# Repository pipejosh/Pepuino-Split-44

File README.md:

### Pepuino Split 44

This is a custom wireless keyboard inpired in the corne and sofle layout so my wrists arent crippled anymore!
A 44 keys keybaord wireless powered by a super mini (the cheapest BT microcontroller I could find) its wirelessssssss btw!
Featuring really cool art and bluetooth connectivity!

### Images

## IRL BUILD!

## Render

## Case

## PCB

## Schematic

## BOM

### Components List

| Name | Purpose | Quantity | Total Cost (USD) | Distributor | Link |
| :--- | :--- | :---: | :---: | :--- | :--- |
| **m2 5mm standoff** | Assembly | 50 | $2.21 | AliExpress | [Link](https://www.aliexpress.com/item/32975966103.html) |
| **m2 2mm screw** | Assembly | 50 | $1.79 | AliExpress | [Link](https://www.aliexpress.com/item/1005005070119421.html) |
| **THT 4.7K resistor** | Pull-up resistor | 20 | $1.77 | AliExpress | [Link](https://www.aliexpress.com/item/1005006704431738.html) |
| **0805 2M Resistor** | Voltage divider | 100 | $1.55 | AliExpress | [Link](https://www.aliexpress.com/item/1005004145810949.html) |
| **0805 820K Resistor** | Voltage divider | 100 | $1.79 | AliExpress | [Link](https://www.aliexpress.com/item/1005004145810949.html) |
| **Battery 3.7V 110mAh** | Keyboard power | 2 | $8.87 | AliExpress | [Link](https://www.google.com/search?q=https://www.aliexpress.com/item/1005011794722407.html) |
| **MSK-12D19** | Slide switch | 20 | $2.05 | AliExpress | [Link](https://www.aliexpress.com/item/1005009651088272.html) |
| **Switches** | Bao Bao Dragon | 45 | $10.95 | AliExpress | [Link](https://www.aliexpress.com/item/1005012005250603.html) |
| **Reset Button** | Reset button | 10 | $2.70 | AliExpress | [Link](https://www.aliexpress.com/item/1005009739698023.html) |
| **SK6812 MINI-E RGB** | RGB Lighting | 50 | $3.86 | AliExpress | [Link](https://www.google.com/search?q=https://www.aliexpress.com/item/1005005193716172.html) |
| **1N4148W T4 SOD-123** | Diodes | 100 | $3.18 | AliExpress | [Link](https://www.aliexpress.com/item/1005007160563285.html) |
| **Hotswap sockets** | Easy replace switches | 50 | $10.13 | AliExpress | [Link](https://www.google.com/search?q=https://www.aliexpress.com/item/1005009254258549.html) |
| **OLED 0.91"** | Display | 2 | $5.52 | AliExpress | [Link](https://www.google.com/search?q=https://www.aliexpress.com/item/1005011783382489.html) |
| **Super mini NRF52840** | Microcontroller | 2 | $5.30 | AliExpress | [Link](https://www.aliexpress.com/item/1005007078900079.html) |
| **Components Subtotal** | | | $61.67 | | |

-----

### PCB Manufacturing

| Name | Purpose | Quantity | Manufacturing | Shipping | Total Cost (USD) | Distributor |
| :--- | :--- | :---: | :---: | :---: | :---: | :--- |
| **PCB** | The main circuit board | 5 | $20.00 | $13.26 | $33.26 | JLCPCB |

-----

**Grand Total Project Estimate Cost: $94.93**

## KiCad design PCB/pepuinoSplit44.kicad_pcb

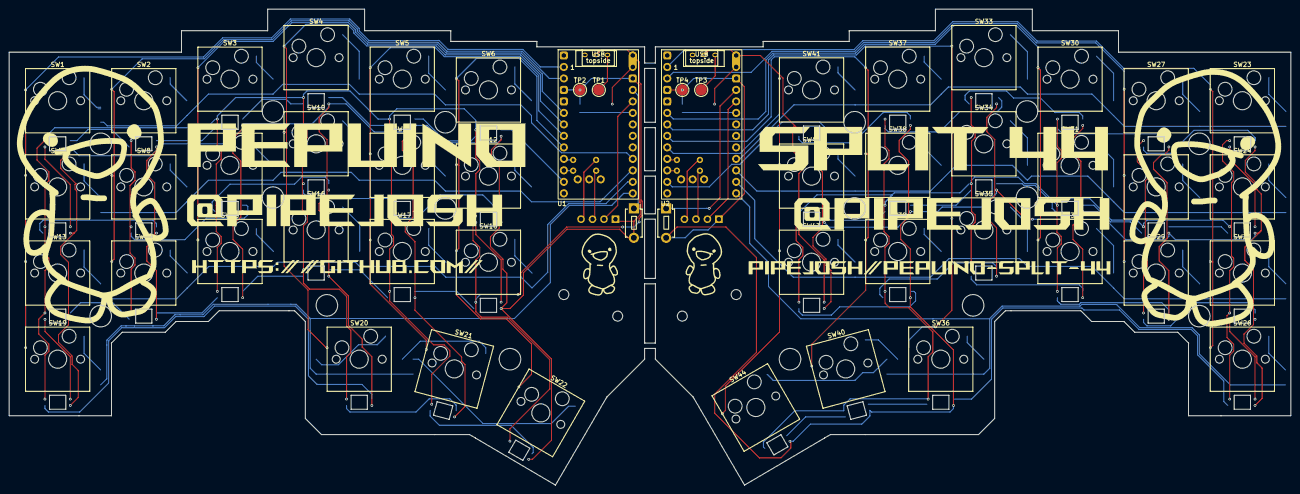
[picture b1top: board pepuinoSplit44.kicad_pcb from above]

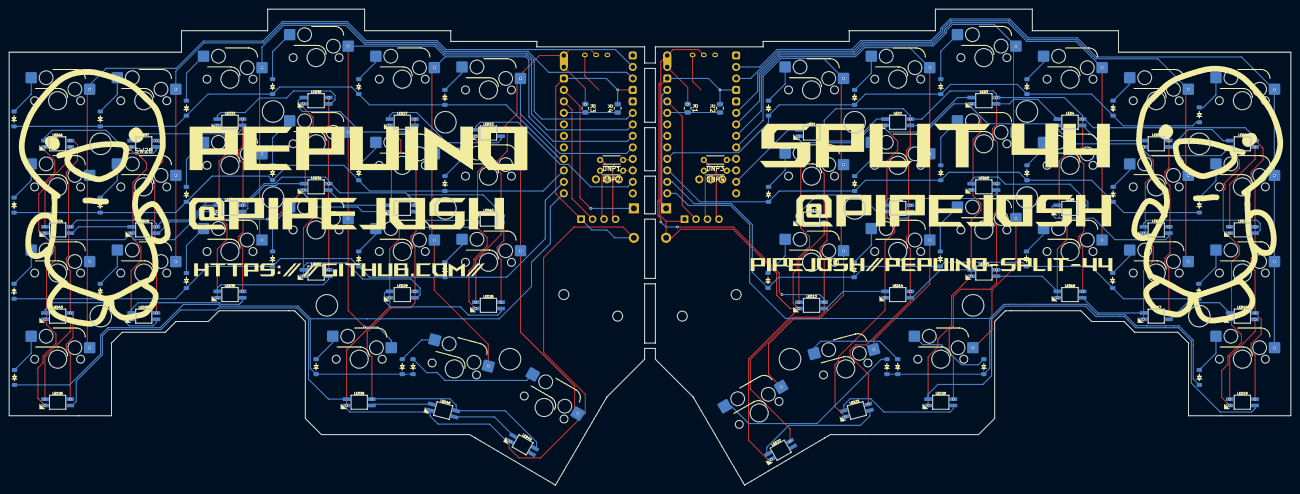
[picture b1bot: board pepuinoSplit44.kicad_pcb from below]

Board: 2 copper layers, 283.3 x 105.2 mm, 156 parts (96 on the bottom side), 128 nets.

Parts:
D1, D2, D3, D4, D5, D6, D7, D8, D9, D10, D11, D12, D13, D14, D15, D16, D17, D18, D19, D20, D21, D22, D23, D24, D25, D26, D27, D28, D29, D30, D31, D32, D33, D34, D35, D36, D37, D38, D39, D40, D41, D42, D43, D44: Diode_SOD-123
DNP1, DNP2, DNP3, DNP4: DNP; R_Axial_DIN0204_L3.6mm_D1.6mm_P5.08mm_Horizontal
H1, H2, H3, H4: MountingHole; MountingHole_2.2mm_M2
J1, J2: OLED_128x32
LED1, LED2, LED3, LED4, LED5, LED6, LED7, LED8, LED9, LED10, LED11, LED12, LED13, LED14, LED15, LED16, LED17, LED18, LED19, LED20, LED21, LED22, LED23, LED24, LED25, LED26, LED27, LED28, LED29, LED30, LED31, LED32, LED33, LED34, LED35, LED36, LED37, LED38, LED39, LED40, LED41, LED42, LED43, LED44: YS-SK6812MINI-E
R1, R3: 806K; R_0805_2012Metric
R2, R4: 2M; R_0805_2012Metric
S1, S2: EG1218; TGSW_MSK-12D19
SW1, SW2, SW3, SW4, SW5, SW6, SW7, SW8, SW9, SW10, SW11, SW12, SW13, SW14, SW15, SW16, SW17, SW18, SW19, SW20, SW21, SW22, SW23, SW24, SW25, SW26, SW27, SW28, SW29, SW30, SW31, SW32, SW33, SW34, SW35, SW36, SW37, SW38, SW39, SW40, SW41, SW42, SW43, SW44: Switch; Hotswap_MX_1.00u
SW45, SW46: Switch; Button_MJTP1243
TP1, TP2, TP3, TP4: TestPoint; TestPoint_Pad_D2.5mm
U1, U2: SuperMini nRF52840; SuperMini_nRF52840_AH_USBup

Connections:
unnamed: D1.2 (A), SW1.2
unnamed: D2.2 (A), SW2.2
unnamed: D3.2 (A), SW3.2
unnamed: D4.2 (A), SW4.2
unnamed: D5.2 (A), SW5.2
unnamed: D6.2 (A), SW6.2
unnamed: D7.2 (A), SW12.2
unnamed: D8.2 (A), SW11.2
unnamed: D9.2 (A), SW10.2
unnamed: D10.2 (A), SW9.2
unnamed: D11.2 (A), SW8.2
unnamed: D12.2 (A), SW7.2
unnamed: D13.2 (A), SW13.2
unnamed: D14.2 (A), SW14.2
unnamed: D15.2 (A), SW15.2
unnamed: D16.2 (A), SW16.2
unnamed: D17.2 (A), SW17.2
unnamed: D18.2 (A), SW18.2
unnamed: D19.2 (A), SW22.2
unnamed: D20.2 (A), SW21.2
unnamed: D21.2 (A), SW20.2
unnamed: D22.2 (A), SW19.2
unnamed: D23.2 (A), SW23.2
unnamed: D24.2 (A), SW24.2
unnamed: D25.2 (A), SW25.2
unnamed: D26.2 (A), SW26.2
unnamed: D27.2 (A), SW27.2
unnamed: D28.2 (A), SW28.2
unnamed: D29.2 (A), SW29.2
unnamed: D30.2 (A), SW30.2
unnamed: D31.2 (A), SW31.2
unnamed: D32.2 (A), SW32.2
unnamed: D33.2 (A), SW33.2
unnamed: D34.2 (A), SW34.2
unnamed: D35.2 (A), SW35.2
unnamed: D36.2 (A), SW36.2
unnamed: D37.2 (A), SW37.2
unnamed: D38.2 (A), SW38.2
unnamed: D39.2 (A), SW39.2
unnamed: D40.2 (A), SW40.2
unnamed: D41.2 (A), SW41.2
unnamed: D42.2 (A), SW42.2
unnamed: D43.2 (A), SW43.2
unnamed: D44.2 (A), SW44.2
unnamed: DNP4.2, J1.3 (SCL)
unnamed: DNP3.2, J1.4 (SDA)
unnamed: DNP2.2, J2.3 (SCL)
unnamed: DNP1.2, J2.4 (SDA)
unnamed: LED1.2 (DOUT), LED2.4 (DIN)
unnamed: LED2.2 (DOUT), LED3.4 (DIN)
unnamed: LED3.2 (DOUT), LED4.4 (DIN)
unnamed: LED4.2 (DOUT), LED5.4 (DIN)
unnamed: LED5.2 (DOUT), LED6.4 (DIN)
unnamed: LED6.2 (DOUT), LED7.4 (DIN)
unnamed: LED7.2 (DOUT), LED8.4 (DIN)
unnamed: LED8.2 (DOUT), LED9.4 (DIN)
unnamed: LED9.2 (DOUT), LED10.4 (DIN)
unnamed: LED10.2 (DOUT), LED11.4 (DIN)
unnamed: LED11.2 (DOUT), LED12.4 (DIN)
unnamed: LED12.2 (DOUT), LED13.4 (DIN)
unnamed: LED13.2 (DOUT), LED14.4 (DIN)
unnamed: LED14.2 (DOUT), LED15.4 (DIN)
unnamed: LED15.2 (DOUT), LED16.4 (DIN)
unnamed: LED16.2 (DOUT), LED17.4 (DIN)
unnamed: LED17.2 (DOUT), LED18.4 (DIN)
unnamed: LED18.2 (DOUT), LED19.4 (DIN)
unnamed: LED19.2 (DOUT), LED20.4 (DIN)
unnamed: LED20.2 (DOUT), LED21.4 (DIN)
unnamed: LED21.2 (DOUT), LED22.4 (DIN)
unnamed: LED23.2 (DOUT), LED27.4 (DIN)
unnamed: LED24.4 (DIN), LED41.2 (DOUT)
unnamed: LED24.2 (DOUT), LED28.4 (DIN)
unnamed: LED25.4 (DIN), LED42.2 (DOUT)
unnamed: LED25.2 (DOUT), LED29.4 (DIN)
unnamed: LED26.4 (DIN), LED43.2 (DOUT)
unnamed: LED26.2 (DOUT), LED36.4 (DIN)
unnamed: LED27.2 (DOUT), LED30.4 (DIN)
unnamed: LED28.2 (DOUT), LED31.4 (DIN)
unnamed: LED29.2 (DOUT), LED32.4 (DIN)
unnamed: LED30.2 (DOUT), LED33.4 (DIN)
unnamed: LED31.2 (DOUT), LED34.4 (DIN)
unnamed: LED32.2 (DOUT), LED35.4 (DIN)
unnamed: LED33.2 (DOUT), LED37.4 (DIN)
unnamed: LED34.2 (DOUT), LED38.4 (DIN)
unnamed: LED35.2 (DOUT), LED39.4 (DIN)
unnamed: LED36.2 (DOUT), LED40.4 (DIN)
unnamed: LED37.2 (DOUT), LED41.4 (DIN)
unnamed: LED38.2 (DOUT), LED42.4 (DIN)
unnamed: LED39.2 (DOUT), LED43.4 (DIN)
unnamed: LED40.2 (DOUT), LED44.4 (DIN)
unnamed: S1.1, TP1.1 (1_1)
unnamed: S2.1, TP3.1 (1_1)
l_3.3V: J1.2 (VCC), U1.16 (3V3)
l_COL0: SW1.1, SW7.1, SW13.1, SW19.1, U1.1 (P0.06)
l_COL1: SW2.1, SW8.1, SW14.1, U1.2 (P0.08)
l_COL2: SW3.1, SW9.1, SW15.1, U1.5 (P0.17)
l_COL3: SW4.1, SW10.1, SW16.1, SW20.1, U1.6 (P0.20)
l_COL4: SW5.1, SW11.1, SW17.1, SW21.1, U1.7 (P0.22)
l_COL5: SW6.1, SW12.1, SW18.1, SW22.1, U1.8 (P0.24)
l_GND: J1.1 (GND), LED1.3 (VSS), LED2.3 (VSS), LED3.3 (VSS), LED4.3 (VSS), LED5.3 (VSS), LED6.3 (VSS), LED7.3 (VSS), LED8.3 (VSS), LED9.3 (VSS), LED10.3 (VSS), LED11.3 (VSS), LED12.3 (VSS), LED13.3 (VSS), LED14.3 (VSS), LED15.3 (VSS), LED16.3 (VSS), LED17.3 (VSS), LED18.3 (VSS), LED19.3 (VSS), LED20.3 (VSS), LED21.3 (VSS), LED22.3 (VSS), R2.2, SW46.2, TP2.1 (1_1), U1.3 (GND), U1.14 (GND)
l_LED: LED1.4 (DIN), U1.11 (P1.04-LF)
l_ROW0: D1.1 (K), D2.1 (K), D3.1 (K), D4.1 (K), D5.1 (K), D6.1 (K), U1.21 (P1.13-LF)
l_ROW1: D7.1 (K), D8.1 (K), D9.1 (K), D10.1 (K), D11.1 (K), D12.1 (K), U1.22 (P1.11-LF)
l_ROW2: D13.1 (K), D14.1 (K), D15.1 (K), D16.1 (K), D17.1 (K), D18.1 (K), U1.23 (P0.10-LF)
l_ROW3: D19.1 (K), D20.1 (K), D21.1 (K), D22.1 (K), U1.24 (P0.09-LF)
l_RST: SW46.1, U1.15 (RST)
l_SCL: DNP4.1, U1.10 (P0.11)
l_SDA: DNP3.1, U1.9 (P1.00)
l_SENSE: R1.2, R2.1, U1.17 (P0.31-LF)
l_VBAT: LED1.1 (VDD), LED2.1 (VDD), LED3.1 (VDD), LED4.1 (VDD), LED5.1 (VDD), LED6.1 (VDD), LED7.1 (VDD), LED8.1 (VDD), LED9.1 (VDD), LED10.1 (VDD), LED11.1 (VDD), LED12.1 (VDD), LED13.1 (VDD), LED14.1 (VDD), LED15.1 (VDD), LED16.1 (VDD), LED17.1 (VDD), LED18.1 (VDD), LED19.1 (VDD), LED20.1 (VDD), LED21.1 (VDD), LED22.1 (VDD), R1.1, S1.2, U1.13 (BAT+), U1.29 (BAT+)
r_3.3V: J2.2 (VCC), U2.16 (3V3)
r_COL0: SW23.1, SW24.1, SW25.1, SW26.1, U2.1 (P0.06)
r_COL1: SW27.1, SW28.1, SW29.1, U2.2 (P0.08)
r_COL2: SW30.1, SW31.1, SW32.1, U2.5 (P0.17)
r_COL3: SW33.1, SW34.1, SW35.1, SW36.1, U2.6 (P0.20)
r_COL4: SW37.1, SW38.1, SW39.1, SW40.1, U2.7 (P0.22)
r_COL5: SW41.1, SW42.1, SW43.1, SW44.1, U2.8 (P0.24)
r_GND: J2.1 (GND), LED23.3 (VSS), LED24.3 (VSS), LED25.3 (VSS), LED26.3 (VSS), LED27.3 (VSS), LED28.3 (VSS), LED29.3 (VSS), LED30.3 (VSS), LED31.3 (VSS), LED32.3 (VSS), LED33.3 (VSS), LED34.3 (VSS), LED35.3 (VSS), LED36.3 (VSS), LED37.3 (VSS), LED38.3 (VSS), LED39.3 (VSS), LED40.3 (VSS), LED41.3 (VSS), LED42.3 (VSS), LED43.3 (VSS), LED44.3 (VSS), R4.2, SW45.2, TP4.1 (1_1), U2.3 (GND), U2.14 (GND)
r_LED: LED23.4 (DIN), U2.11 (P1.04-LF)
r_ROW0: D23.1 (K), D27.1 (K), D30.1 (K), D33.1 (K), D37.1 (K), D41.1 (K), U2.21 (P1.13-LF)
r_ROW1: D24.1 (K), D28.1 (K), D31.1 (K), D34.1 (K), D38.1 (K), D42.1 (K), U2.22 (P1.11-LF)
r_ROW2: D25.1 (K), D29.1 (K), D32.1 (K), D35.1 (K), D39.1 (K), D43.1 (K), U2.23 (P0.10-LF)
r_ROW3: D26.1 (K), D36.1 (K), D40.1 (K), D44.1 (K), U2.24 (P0.09-LF)
r_RST: SW45.1, U2.15 (RST)
r_SCL: DNP2.1, U2.10 (P0.11)
r_SDA: DNP1.1, U2.9 (P1.00)
r_SENSE: R3.2, R4.1, U2.17 (P0.31-LF)
r_VBAT: LED23.1 (VDD), LED24.1 (VDD), LED25.1 (VDD), LED26.1 (VDD), LED27.1 (VDD), LED28.1 (VDD), LED29.1 (VDD), LED30.1 (VDD), LED31.1 (VDD), LED32.1 (VDD), LED33.1 (VDD), LED34.1 (VDD), LED35.1 (VDD), LED36.1 (VDD), LED37.1 (VDD), LED38.1 (VDD), LED39.1 (VDD), LED40.1 (VDD), LED41.1 (VDD), LED42.1 (VDD), LED43.1 (VDD), LED44.1 (VDD), R3.1, S2.2, U2.13 (BAT+), U2.29 (BAT+)

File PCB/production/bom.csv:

Designator,Footprint,Quantity,Value,LCSC Part #
"D1, D10, D11, D12, D13, D14, D15, D16, D17, D18, D19, D2, D20, D21, D22, D23, D24, D25, D26, D27, D28, D29, D3, D30, D31, D32, D33, D34, D35, D36, D37, D38, D39, D4, D40, D41, D42, D43, D44, D5, D6, D7, D8, D9",Diode_SOD-123,44,~,
"J1, J2",OLED_128x32,2,OLED_128x32,
"LED1, LED10, LED11, LED12, LED13, LED14, LED15, LED16, LED17, LED18, LED19, LED2, LED20, LED21, LED22, LED23, LED24, LED25, LED26, LED27, LED28, LED29, LED3, LED30, LED31, LED32, LED33, LED34, LED35, LED36, LED37, LED38, LED39, LED4, LED40, LED41, LED42, LED43, LED44, LED5, LED6, LED7, LED8, LED9",YS-SK6812MINI-E,44,YS-SK6812MINI-E,
"R1, R3",0805,2,806K,
"R2, R4",0805,2,2M,
"S1, S2",TGSW_MSK-12D19,2,EG1218,
"SW1, SW10, SW11, SW12, SW13, SW14, SW15, SW16, SW17, SW18, SW19, SW2, SW20, SW21, SW22, SW23, SW24, SW25, SW26, SW27, SW28, SW29, SW3, SW30, SW31, SW32, SW33, SW34, SW35, SW36, SW37, SW38, SW39, SW4, SW40, SW41, SW42, SW43, SW44, SW5, SW6, SW7, SW8, SW9",Hotswap_MX_1.00u,44,Switch,
"SW45, SW46",Button_MJTP1243,2,Switch,
"TP1, TP2, TP3, TP4",TestPoint_Pad_D2.5mm,4,TestPoint,

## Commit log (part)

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2026-03-19 intintal commit
2026-04-01 organize
2026-04-05 create md + organize + update case
2026-04-05 add BOM
2026-04-11 Update readme + BOM + pcb + add firmware
2026-04-11 fix reamde table
2026-04-11 fix table again
